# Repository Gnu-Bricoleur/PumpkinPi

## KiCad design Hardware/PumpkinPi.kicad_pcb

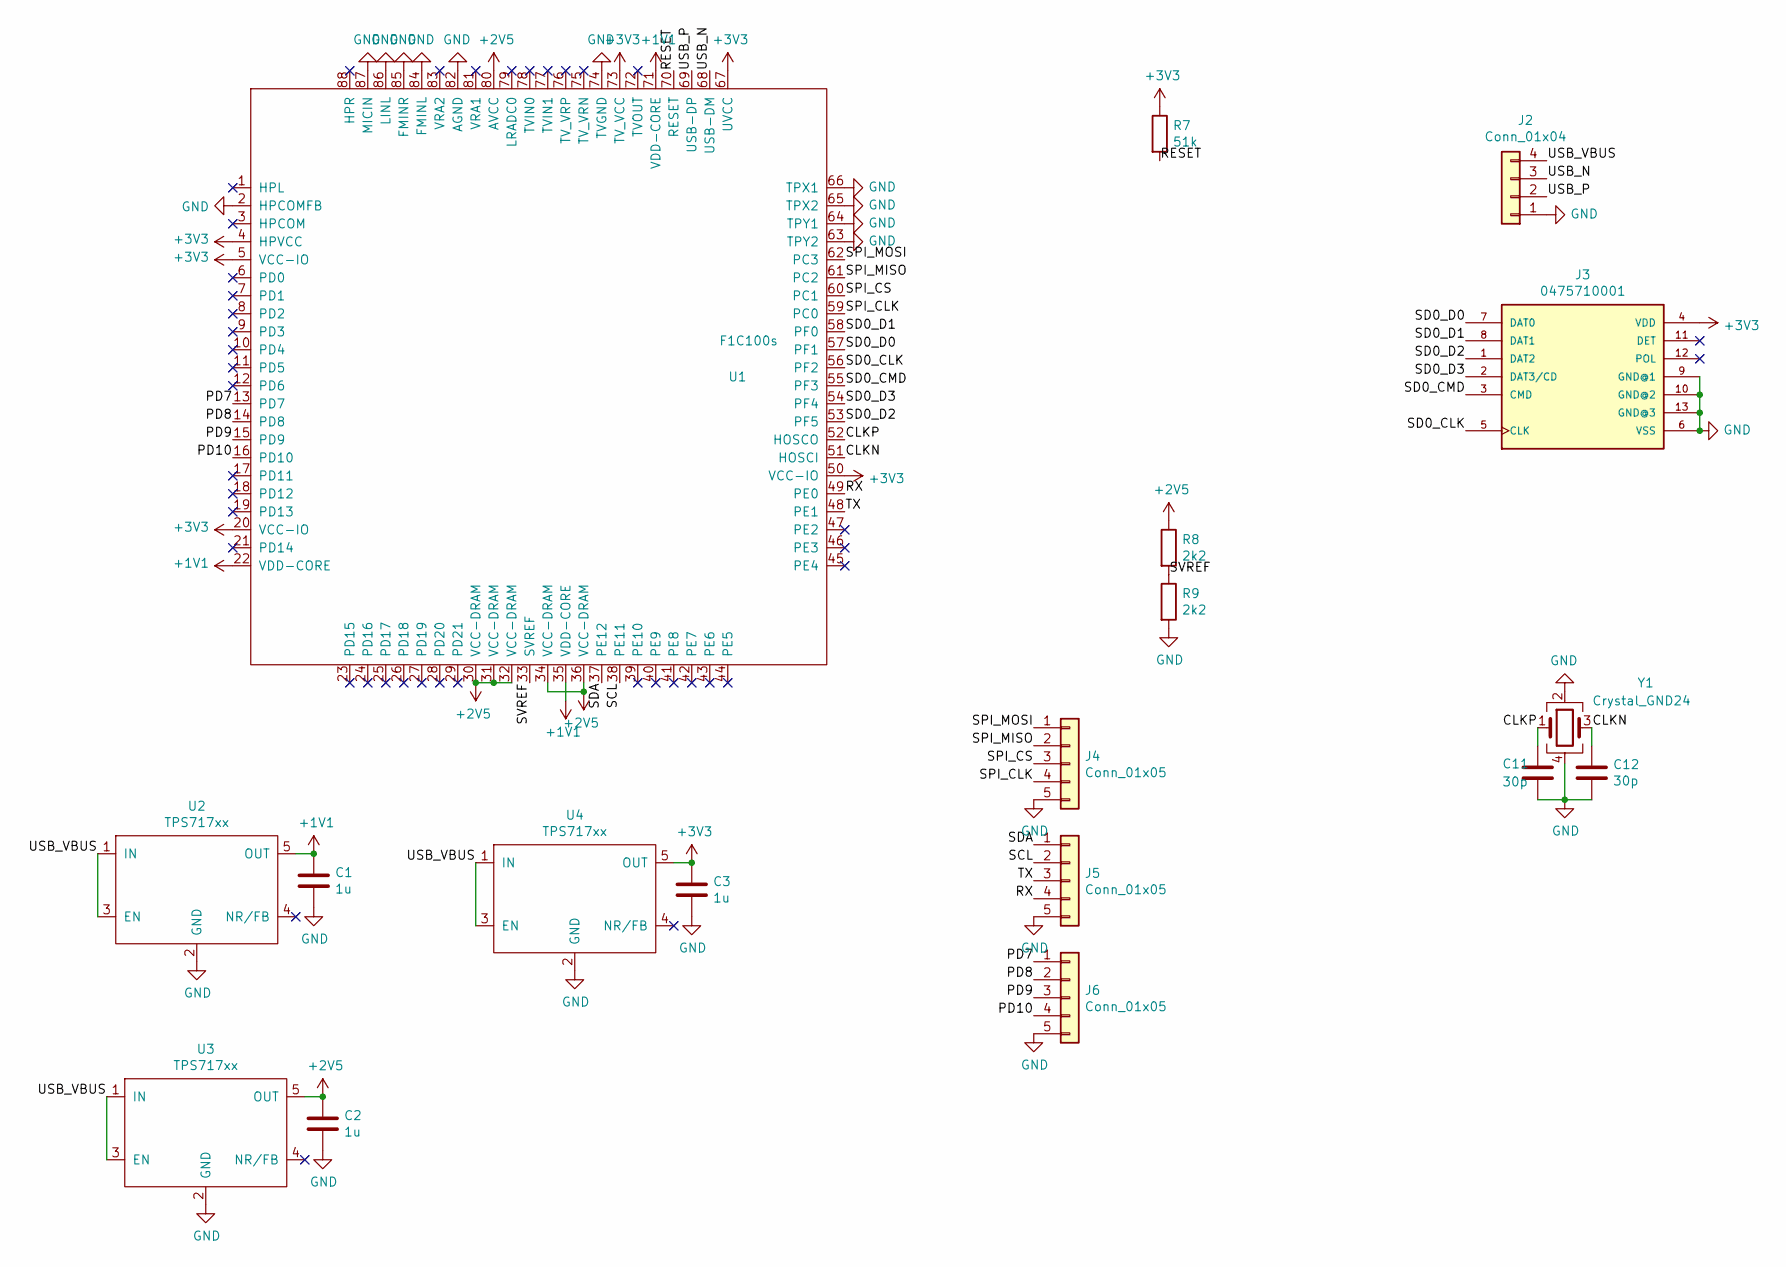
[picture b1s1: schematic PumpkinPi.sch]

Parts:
C1, C2, C3: 1u; C_0402_1005Metric_Pad0.74x0.62mm_HandSolder
C11, C12: 30p; C_0402_1005Metric_Pad0.74x0.62mm_HandSolder
J2: Conn_01x04; USB_PCB
J3: 0475710001; MOLEX_0475710001
J4, J5, J6: Conn_01x05; PinHeader_1x05_P2.54mm_Vertical
R7: 51k; R_0402_1005Metric_Pad0.72x0.64mm_HandSolder
R8, R9: 2k2; R_0402_1005Metric_Pad0.72x0.64mm_HandSolder
U1: F1C100s; QFN-88_EP_10x10_Pitch0.4mm
U2, U3, U4: TPS717xx; SOT-353_SC-70-5
Y1: Crystal_GND24; Crystal_SMD_5032-4Pin_5.0x3.2mm

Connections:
+1V1: C1.1, U1.22 (VDD-CORE), U1.35 (VDD-CORE), U1.71 (VDD-CORE), U2.5 (OUT)
+2V5: C2.1, R8.1, U1.30 (VCC-DRAM), U1.31 (VCC-DRAM), U1.32 (VCC-DRAM), U1.34 (VCC-DRAM), U1.36 (VCC-DRAM), U1.80 (AVCC), U3.5 (OUT)
+3V3: C3.1, J3.4 (VDD), R7.1, U1.4 (HPVCC), U1.5 (VCC-IO), U1.20 (VCC-IO), U1.50 (VCC-IO), U1.67 (UVCC), U1.73 (TV_VCC), U4.5 (OUT)
/CLKN: C12.1, U1.51 (HOSCI), Y1.3
/CLKP: C11.1, U1.52 (HOSCO), Y1.1
/PD7: J6.1, U1.13 (PD7)
/PD8: J6.2, U1.14 (PD8)
/PD9: J6.3, U1.15 (PD9)
/PD10: J6.4, U1.16 (PD10)
/RESET: R7.2, U1.70 (RESET)
/RX: J5.4, U1.49 (PE0)
/SCL: J5.2, U1.38 (PE11)
/SD0_CLK: J3.5 (CLK), U1.56 (PF2)
/SD0_CMD: J3.3 (CMD), U1.55 (PF3)
/SD0_D0: J3.7 (DAT0), U1.57 (PF1)
/SD0_D1: J3.8 (DAT1), U1.58 (PF0)
/SD0_D2: J3.1 (DAT2), U1.53 (PF5)
/SD0_D3: J3.2 (DAT3/CD), U1.54 (PF4)
/SDA: J5.1, U1.37 (PE12)
/SPI_CLK: J4.4, U1.59 (PC0)
/SPI_CS: J4.3, U1.60 (PC1)
/SPI_MISO: J4.2, U1.61 (PC2)
/SPI_MOSI: J4.1, U1.62 (PC3)
/SVREF: R8.2, R9.1, U1.33 (SVREF)
/TX: J5.3, U1.48 (PE1)
/USB_N: J2.3, U1.68 (USB-DM)
/USB_P: J2.2, U1.69 (USB-DP)
/USB_VBUS: J2.4, U2.1 (IN), U2.3 (EN), U3.1 (IN), U3.3 (EN), U4.1 (IN), U4.3 (EN)
GND: C1.2, C2.2, C3.2, C11.2, C12.2, J2.1, J3.6 (VSS), J3.9 (GND@1), J3.10 (GND@2), J3.13 (GND@3), J4.5, J5.5, J6.5, R9.2, U1.2 (HPCOMFB), U1.63 (TPY2), U1.64 (TPY1), U1.65 (TPX2), U1.66 (TPX1), U1.74 (TVGND), U1.82 (AGND), U1.84 (FMINL), U1.85 (FMINR), U1.86 (LINL), U1.87 (MICIN), U2.2 (GND), U3.2 (GND), U4.2 (GND), Y1.2, Y1.4

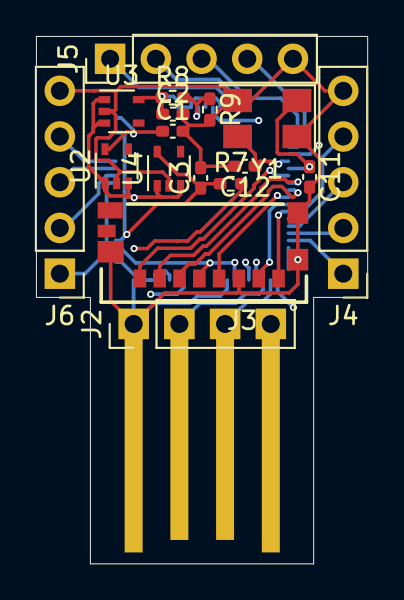
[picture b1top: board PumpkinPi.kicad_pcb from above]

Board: 4 copper layers, 18.4 x 29.3 mm, 18 parts (1 on the bottom side), 29 nets.

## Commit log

2021-07-15 draft of F1C100s footprint
2021-07-15 move schematics to dedicated folder
2021-07-15 add pin numbers
2021-07-15 starting wiring
2021-07-15 wiring progress
2021-07-17 wiring in progress
2021-07-18 wiring in progress ..
2021-07-18 USB connector
2021-07-19 progress on wiring
2021-07-20 progress ...
2021-08-04 huge progress
2021-08-04 schemqtic finished, routing started
2021-08-05 minor changes
2021-08-05 placemnt done
2021-08-06 routing done
2021-08-06 gerbers
2022-06-21 Updated to KiCAD 6
